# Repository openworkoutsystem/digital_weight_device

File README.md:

# Project Overview: Open-Source Smart Fitness

Open Workout System is an open-source community creating a high-fidelity smart health/fitness device dedicated to improving your fitness and health. Our primary goal is to develop cost-conscious, accessible, and safe workout systems that cater to a broad audience, from general fitness enthusiasts to individuals undergoing physical therapy. By leveraging open-source principles, we aim to foster a community of developers, fitness professionals, and users who can collaborate to continually improve and expand our solutions.

### V4 Design Readme --> [V4 Design Readme](README_V4DESIGN.md)

### What's Different About This Project/Fitness Solution?

- Completely open source
- 11 lb device that can emulate up to 200 lb (exact specs in design)
- Fully wireless
- Use it anywhere: on the floor, with a door, wall, etc.
- Measures everything you want: power, speed, rep counter, timing
- Benchmarks your fitness
- Tracks your physical therapy progress
- Physical therapists will be able to design and monitor your progress for recovery (remotely and locally)
- Gamify your workout: We're excited to see how this device will be integrated in fun new ways to enhance your routine.

The ultra-compact BLDC motor-driven workout system is our core design focus, aimed at providing a comprehensive, safe, and affordable fitness solution. Traditional workout systems can be intimidating due to their size, complexity, and cost. Our system is ultra-compact and easy to use, ensuring it fits seamlessly into your life. The body-friendly strap enhances safety over a traditional cable system.

### Why Open Source?

As an open-source project, we believe in the power of community and collaboration. By making our designs, code, and documentation freely available, we enable others to contribute to the project, helping to accelerate innovation and bring high-quality fitness solutions to more people. Our commitment to open source ensures transparency, adaptability, and continuous improvement.

Hardware is hard. We want to provide access to a fantastic and safe fitness device for others to build their creative ideas on! Our philosophy is that we make you better, you make us better, and we're all better for it. We know, like us, there are others with great ideas on how to improve their daily routines and unique needs.

### Contribution

We welcome contributions to our project! Whether it's code, hardware designs, documentation, or testing, your input is valuable. To get started please join our Discord Community --> [Open Workout System Discord Server](https://discord.gg/DzmPTt3dUt)
For more information, questions, or collaboration inquiries, please contact us at [aaron.willey+ows@gmail.com].

### Safety and Accessibility

Safety is paramount in our design philosophy. Our Digital Weight Workout System includes features such as device movement sensing, dropped handle detection, and programmable safety limits to ensure a safe workout experience. The lower cost of entry allows a wider audience to access this advanced technology, promoting health and fitness across various demographics. Our goal is to provide a safer and more effective alternative to traditional free weights, reducing the risk of injury and making fitness accessible to all.

## Outline of Project Repositories

- **Digital Weight Device**: The main fitness device central to this project.
- **Applications that communicate with the digital weight**:
  - Web app (simple PWA interface for testing)
  - Mobile app - coming soon
  - Watch app - coming soon
- **Remote device**: Smart controller/remote for the digital weight.
- **Game demos**: Example integration of the device with different games for exploration of use ideas.

### Device Highlights

- **11 lb device**
- **Strength training up to 200 lb (400 lb 2X)**
- **Adaptive rowing and paddling modes**
- **Simple controls (mechanical and touch)**
- **Fully wireless**
- **Self-charging modes**
- **No installation required**
- **Safety features**:
  - Body-friendly strap (no cables)
  - Device movement sensing
  - Dropped handle detection
  - Programmable safety limits
  - Resistance only operation mode

### License

This project is licensed under the terms of the MIT license. See the [LICENSE](LICENSE) file for details.

## Digital Weight Workout System

### Images and Features

#### v4 Pictures

<!-- - 
- 
- 
- 
- 
-  -->

## Older v1_v2_v3 Pictures

<!-- - 
-  -->

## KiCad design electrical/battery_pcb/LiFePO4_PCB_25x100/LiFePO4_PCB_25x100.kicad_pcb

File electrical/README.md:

# Schematics for V4 coming soon

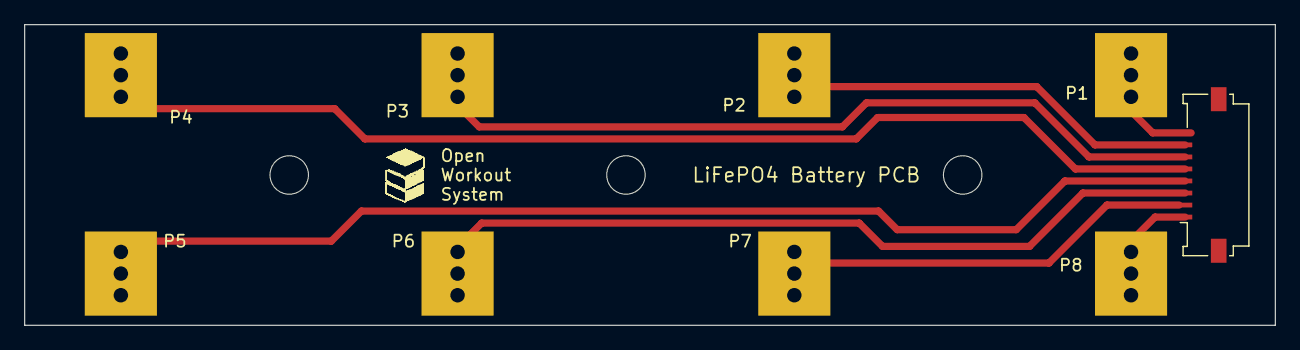
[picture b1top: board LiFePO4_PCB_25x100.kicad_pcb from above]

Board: 2 copper layers, 104.0 x 25.0 mm, 8 parts (0 on the bottom side), 8 nets.

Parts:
P1, P2, P3, P4, P5, P6, P7, P8: BattPad; BatteryPad_Edge

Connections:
Net1: P1.1, P1.3, P1.4
Net2: P2.1, P2.2, P2.4
Net3: P3.1, P3.3
Net4: P4.1, P4.4
Net5: P5.1, P5.2, P5.3, P5.4
Net6: P6.1, P6.2, P6.3, P6.4
Net7: P7.1, P7.2, P7.3, P7.4
Net8: P8.1, P8.2, P8.3, P8.4

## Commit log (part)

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2024-06-22 initial release
2024-06-22 Created LICENSE
2024-06-22 folder sync
2024-06-22 first cad upload
2024-06-22 added description
2024-06-22 readme update
2024-06-22 corrected
2024-06-22 details
2024-06-22 new cad images
2024-06-22 docs: Update README with V5 next steps and image preview
2024-06-22 feat: Add new files for SquareLine GUI and fonts
    The commit adds new files for the SquareLine GUI, including event handling functions and font configuration files.
2024-06-22 feat: Add SquareLine GUI files and update README
    This commit adds the necessary files for the SquareLine GUI, including event handling functions and font configuration files. Additionally, the README has been updated with information about the V5 n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
2024-06-22 feat: Add SquareLine GUI files and update README
2024-06-23 feat: Generate Bill of Materials (BOM) markdown file
2024-06-23 refactor: Update BOM item numbering logic
2024-06-23 feat: Add V4 BOM link to README
2024-06-23 feat: Update README with V4 BOM link
2024-06-23 folder restructure
2024-06-24 feat: Add motor data CSV and stats markdown files
2024-06-28 Update motor_data.csv with corrected weight for Cube Mars RO100 Frameless kv55 motor
2024-06-28 Update motor weight to 750 grams
2024-06-28 chore: Update .gitignore to ignore VSCode settings and PlatformIO build artifacts
2024-06-28 Update .gitignore to ignore VSCode settings and PlatformIO build artifacts
2024-06-29 chore: Remove unnecessary LVGL files
2024-06-30 added step files
2024-06-30 feat: Update Digital Weight V4 documentation with known issues and limitations
2024-06-30 Update README.md with improved project philosophy and contribution section
2025-10-04 Add Read the Docs configuration file
    This configuration file sets up Read the Docs with the specified Python version and build settings.
2025-10-04 adding initial rtd
2025-10-04 rtd fix
2025-10-04 rtd fix attempt
2025-10-04 rtd working. updated look
2025-10-04 gh pages
2025-10-04 ghp update
2025-10-04 ghp fix attempt
2025-10-04 Create CNAME
2025-10-04 added build_docs.bat
2025-11-05 faster screen load, wifi client websocket
